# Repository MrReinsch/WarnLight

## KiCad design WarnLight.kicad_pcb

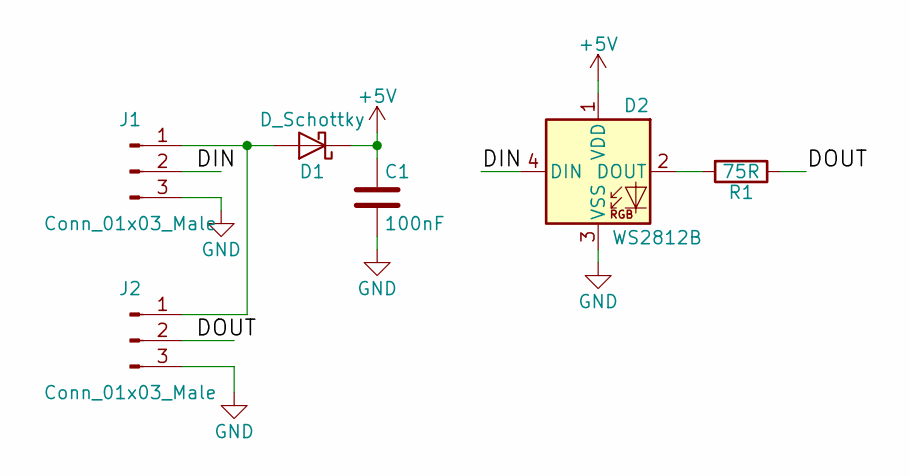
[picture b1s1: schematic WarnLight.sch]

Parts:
C1: 100nF; C_0805_HandSoldering
D1: D_Schottky; D_SMA_Handsoldering
D2: WS2812B; LED_WS2812B-PLCC4
J1, J2: Conn_01x03_Male; Pin_Header_Straight_1x03_Pitch2.54mm
R1: 75R; R_0805_HandSoldering

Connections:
+5V: C1.1, D1.1 (K), D2.1 (VDD)
/DIN: D2.4 (DIN), J1.2
/DOUT: J2.2, R1.1
GND: C1.2, D2.3 (VSS), J1.3, J2.3
unnamed: D1.2 (A), J1.1, J2.1
unnamed: D2.2 (DOUT), R1.2

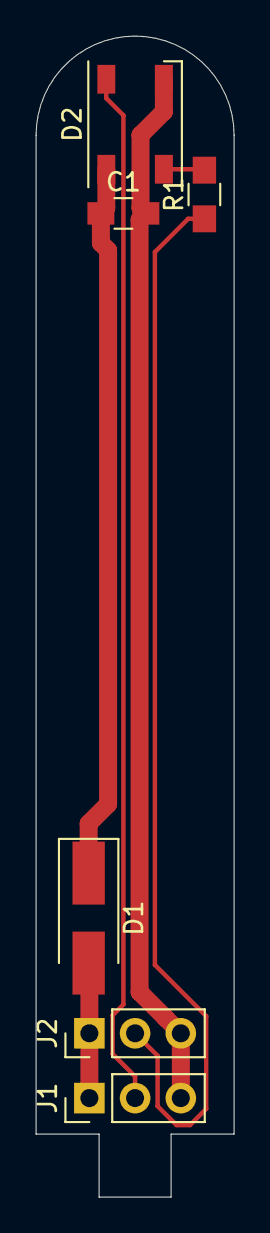
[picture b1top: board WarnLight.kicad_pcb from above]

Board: 2 copper layers, 11.0 x 64.5 mm, 6 parts (0 on the bottom side), 6 nets.

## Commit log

2019-03-19 first version
2019-03-21 panel
